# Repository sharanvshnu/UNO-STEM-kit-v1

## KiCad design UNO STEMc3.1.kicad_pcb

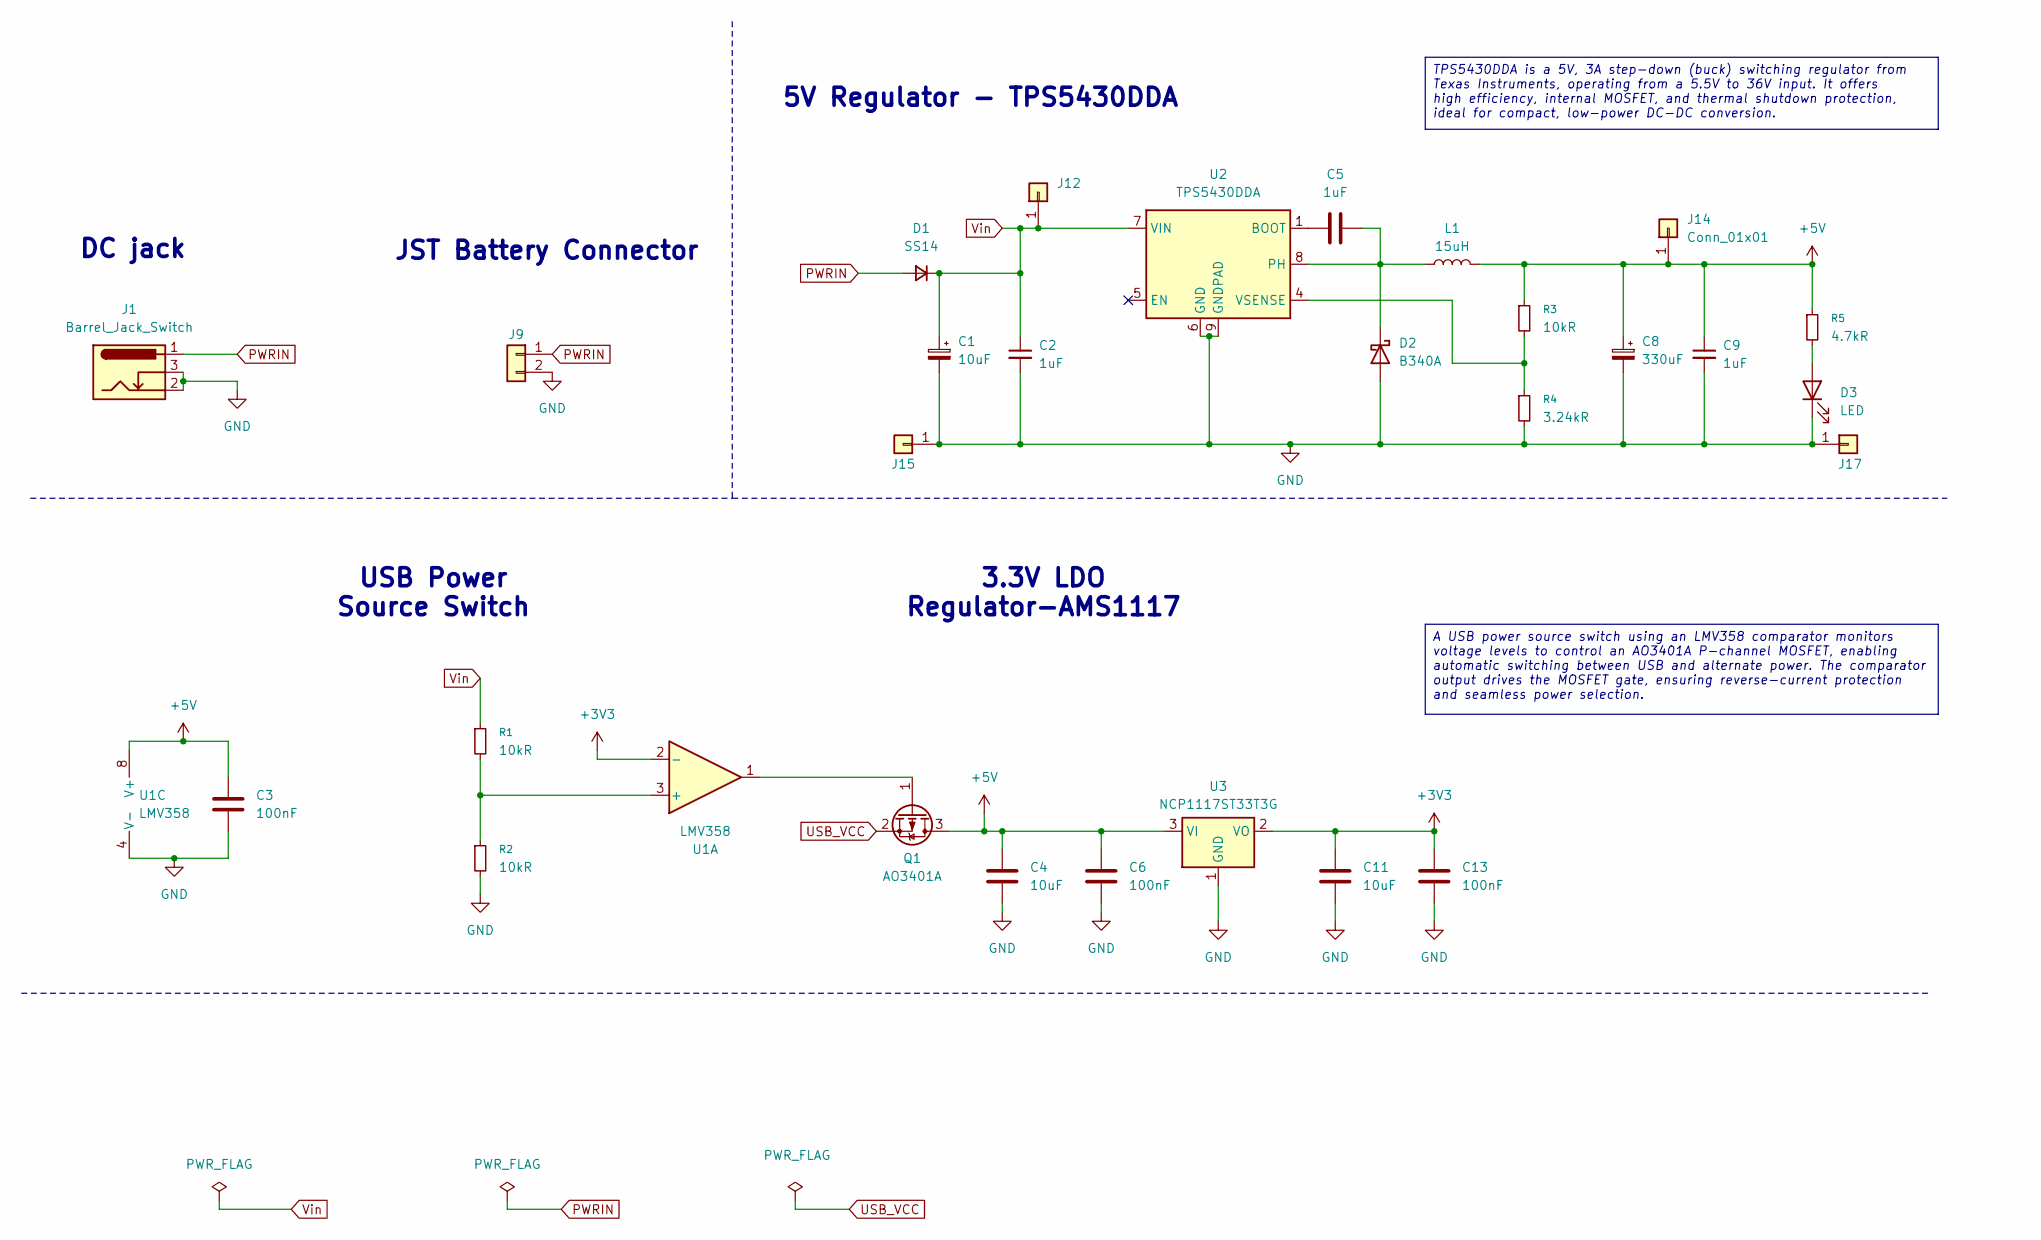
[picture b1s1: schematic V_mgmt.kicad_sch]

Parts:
C1: 10uF; CP_Elec_5x5.3
C2, C5, C9: 1uF; C_0805_2012Metric
C3, C6, C13: 100nF; C_0805_2012Metric
C4, C11: 10uF; C_0805_2012Metric
C8: 330uF; CP_Elec_10x10.5
D1: SS14; D_SMA
D2: B340A; D_SMA
D3: LED; LED_0805_2012Metric
J1: Barrel_Jack_Switch; BarrelJack_GCT_DCJ200-10-A_Horizontal
J9: Conn_01x02; PinHeader_1x02_P2.54mm_Vertical
J12, J14, J15, J17: Conn_01x01; PinHeader_1x01_P2.54mm_Vertical
L1: 15uH; L_10.4x10.4_H4.8
Q1: AO3401A; SOT-23
R1, R2, R3: 10kR; R_0402_1005Metric
R4: 3.24kR; R_0402_1005Metric
R5: 4.7kR; R_0402_1005Metric
U1: LMV358; SOIC-8_3.9x4.9mm_P1.27mm
U2: TPS5430DDA; TI_SO-PowerPAD-8_ThermalVias
U3: NCP1117ST33T3G; SOT-223-3_TabPin2

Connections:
+3V3: C11.1, C13.1, U1.2 (-), U3.2 (VO); also elsewhere on the board
+5V: C3.1, C4.1, C6.1, C8.1, C9.1, J14.1, L1.2, Q1.3 (D), R3.1, R5.1, U1.8 (V+), U3.3 (VI); also elsewhere on the board
GND: C1.2, C2.2, C3.2, C4.2, C6.2, C8.2, C9.2, C11.2, C13.2, D2.2 (A), D3.1 (K), J1.2, J1.3, J9.2, J15.1, J17.1, R2.2, R4.2, U1.4 (V-), U2.6 (GND), U2.9 (GNDPAD), U3.1 (GND); also elsewhere on the board
unnamed: C5.2, D2.1 (K), L1.1, U2.8 (PH)
unnamed: D3.2 (A), R5.2
unnamed: Q1.1 (G), U1.1
unnamed: R1.2, R2.1, U1.3 (+)
unnamed: C5.1, U2.1 (BOOT)
unnamed: R3.2, R4.1, U2.4 (VSENSE)
PWRIN: D1.2 (A), J1.1, J9.1
USB_VCC: Q1.2 (S); also elsewhere on the board
Vin: C1.1, C2.1, D1.1 (K), J12.1, R1.1, U2.7 (VIN)

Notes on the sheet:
JST Battery Connector
3.3V LDO Regulator-AMS1117
5V Regulator - TPS5430DDA
USB Power Source Switch
DC jack
TPS5430DDA is a 5V, 3A step-down (buck) switching regulator from Texas Instruments, operating from a 5.5V to 36V input. It offers high efficiency, internal MOSFET, and thermal shutdown protection, ideal for compact, low-power DC-DC conversion.
A USB power source switch using an LMV358 comparator monitors voltage levels to control an AO3401A P-channel MOSFET, enabling automatic switching between USB and alternate power. The comparator output drives the MOSFET gate, ensuring reverse-current protection and seamless power selection.

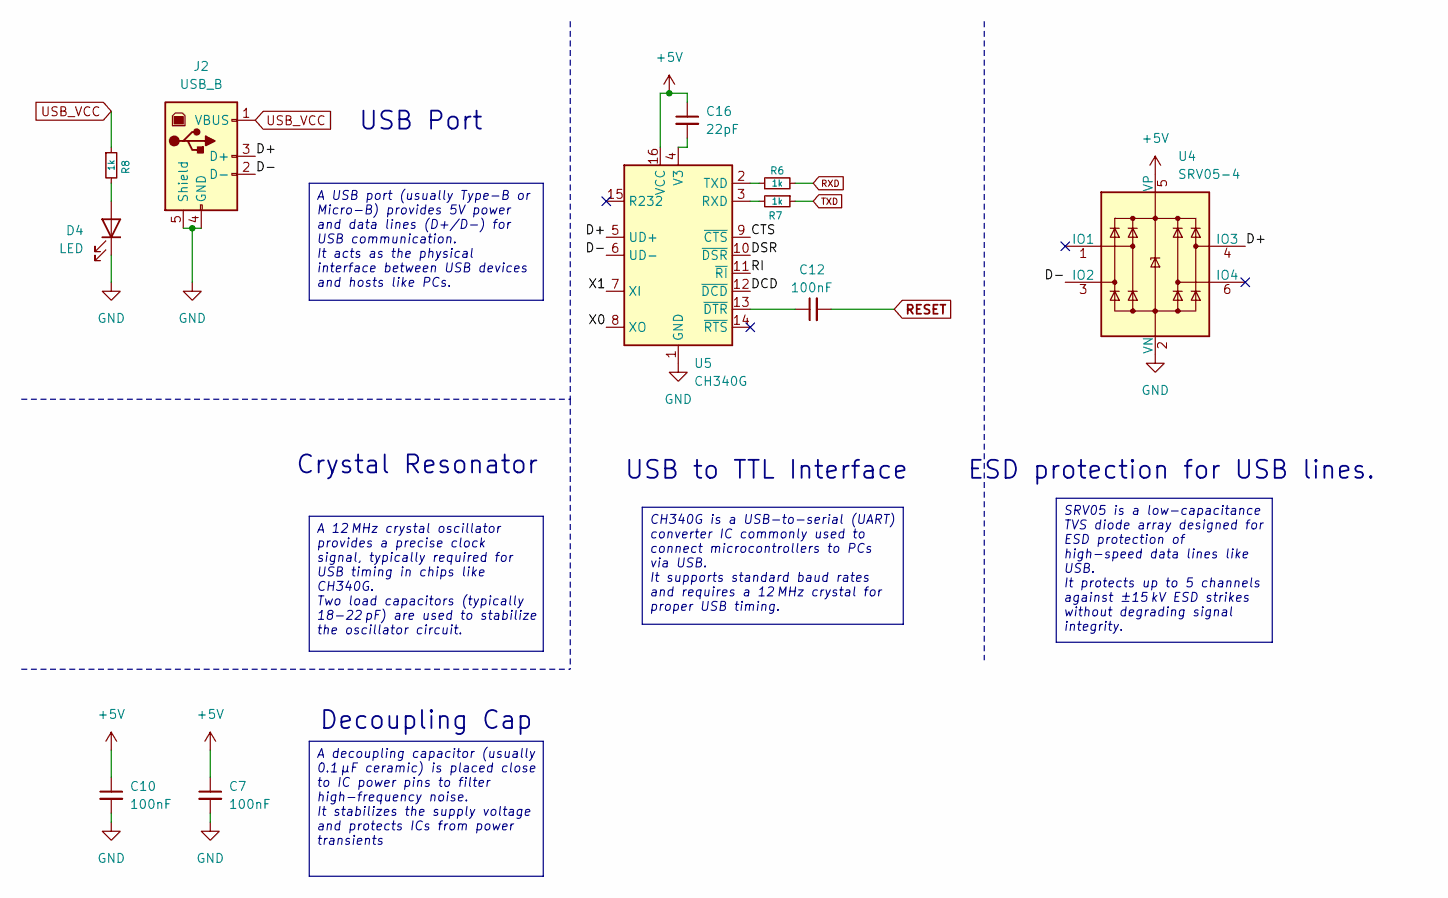
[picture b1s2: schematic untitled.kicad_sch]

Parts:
C7, C10, C12: 100nF; C_0805_2012Metric
C16: 22pF; C_0805_2012Metric
D4: LED; LED_0805_2012Metric
J2: USB_B; USB_B_Lumberg_2411_02_Horizontal
R6, R7: 1k; R_0402_1005Metric
R8: 1k; R_0603_1608Metric
U4: SRV05-4; SOT-23-6
U5: CH340G; SOIC-16_3.9x9.9mm_P1.27mm

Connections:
+5V: C7.1, C10.1, C16.1, U4.5 (VP), U5.16 (VCC); also elsewhere on the board
/USB-TTL/CTS: U5.9 (~CTS)
/USB-TTL/D+: J2.3 (D+), U4.4 (IO3), U5.5 (UD+)
/USB-TTL/D-: J2.2 (D-), U4.3 (IO2), U5.6 (UD-)
/USB-TTL/DCD: U5.12 (~DCD)
/USB-TTL/DSR: U5.10 (~DSR)
/USB-TTL/RI: U5.11 (~RI)
/USB-TTL/X0: U5.8 (XO)
/USB-TTL/X1: U5.7 (XI)
GND: C7.2, C10.2, D4.1 (K), J2.4 (GND), J2.5 (Shield), U4.2 (VN), U5.1 (GND); also elsewhere on the board
unnamed: D4.2 (A), R8.2
unnamed: R7.2, U5.3 (RXD)
unnamed: R6.1, U5.2 (TXD)
unnamed: C16.2, U5.4 (V3)
unnamed: C12.1, U5.13 (~DTR)
RESET: C12.2; also elsewhere on the board
RXD: R6.2; also elsewhere on the board
TXD: R7.1; also elsewhere on the board
USB_VCC: J2.1 (VBUS), R8.1; also elsewhere on the board

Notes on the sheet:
Crystal Resonator
USB to TTL Interface
Decoupling Cap
ESD protection for USB lines.
USB Port
SRV05 is a low-capacitance TVS diode array designed for ESD protection of high-speed data lines like USB. It protects up to 5 channels against ±15 kV ESD strikes without degrading signal integrity.
A USB port (usually Type-B or Micro-B) provides 5V power and data lines (D+/D−) for USB communication. It acts as the physical interface between USB devices and hosts like PCs.
A decoupling capacitor (usually 0.1 µF ceramic) is placed close to IC power pins to filter high-frequency noise. It stabilizes the supply voltage and protects ICs from power transients
A 12 MHz crystal oscillator provides a precise clock signal, typically required for USB timing in chips like CH340G. Two load capacitors (typically 18-22 pF) are used to stabilize the oscillator circuit.
CH340G is a USB-to-serial (UART) converter IC commonly used to connect microcontrollers to PCs via USB. It supports standard baud rates and requires a 12 MHz crystal for proper USB timing.

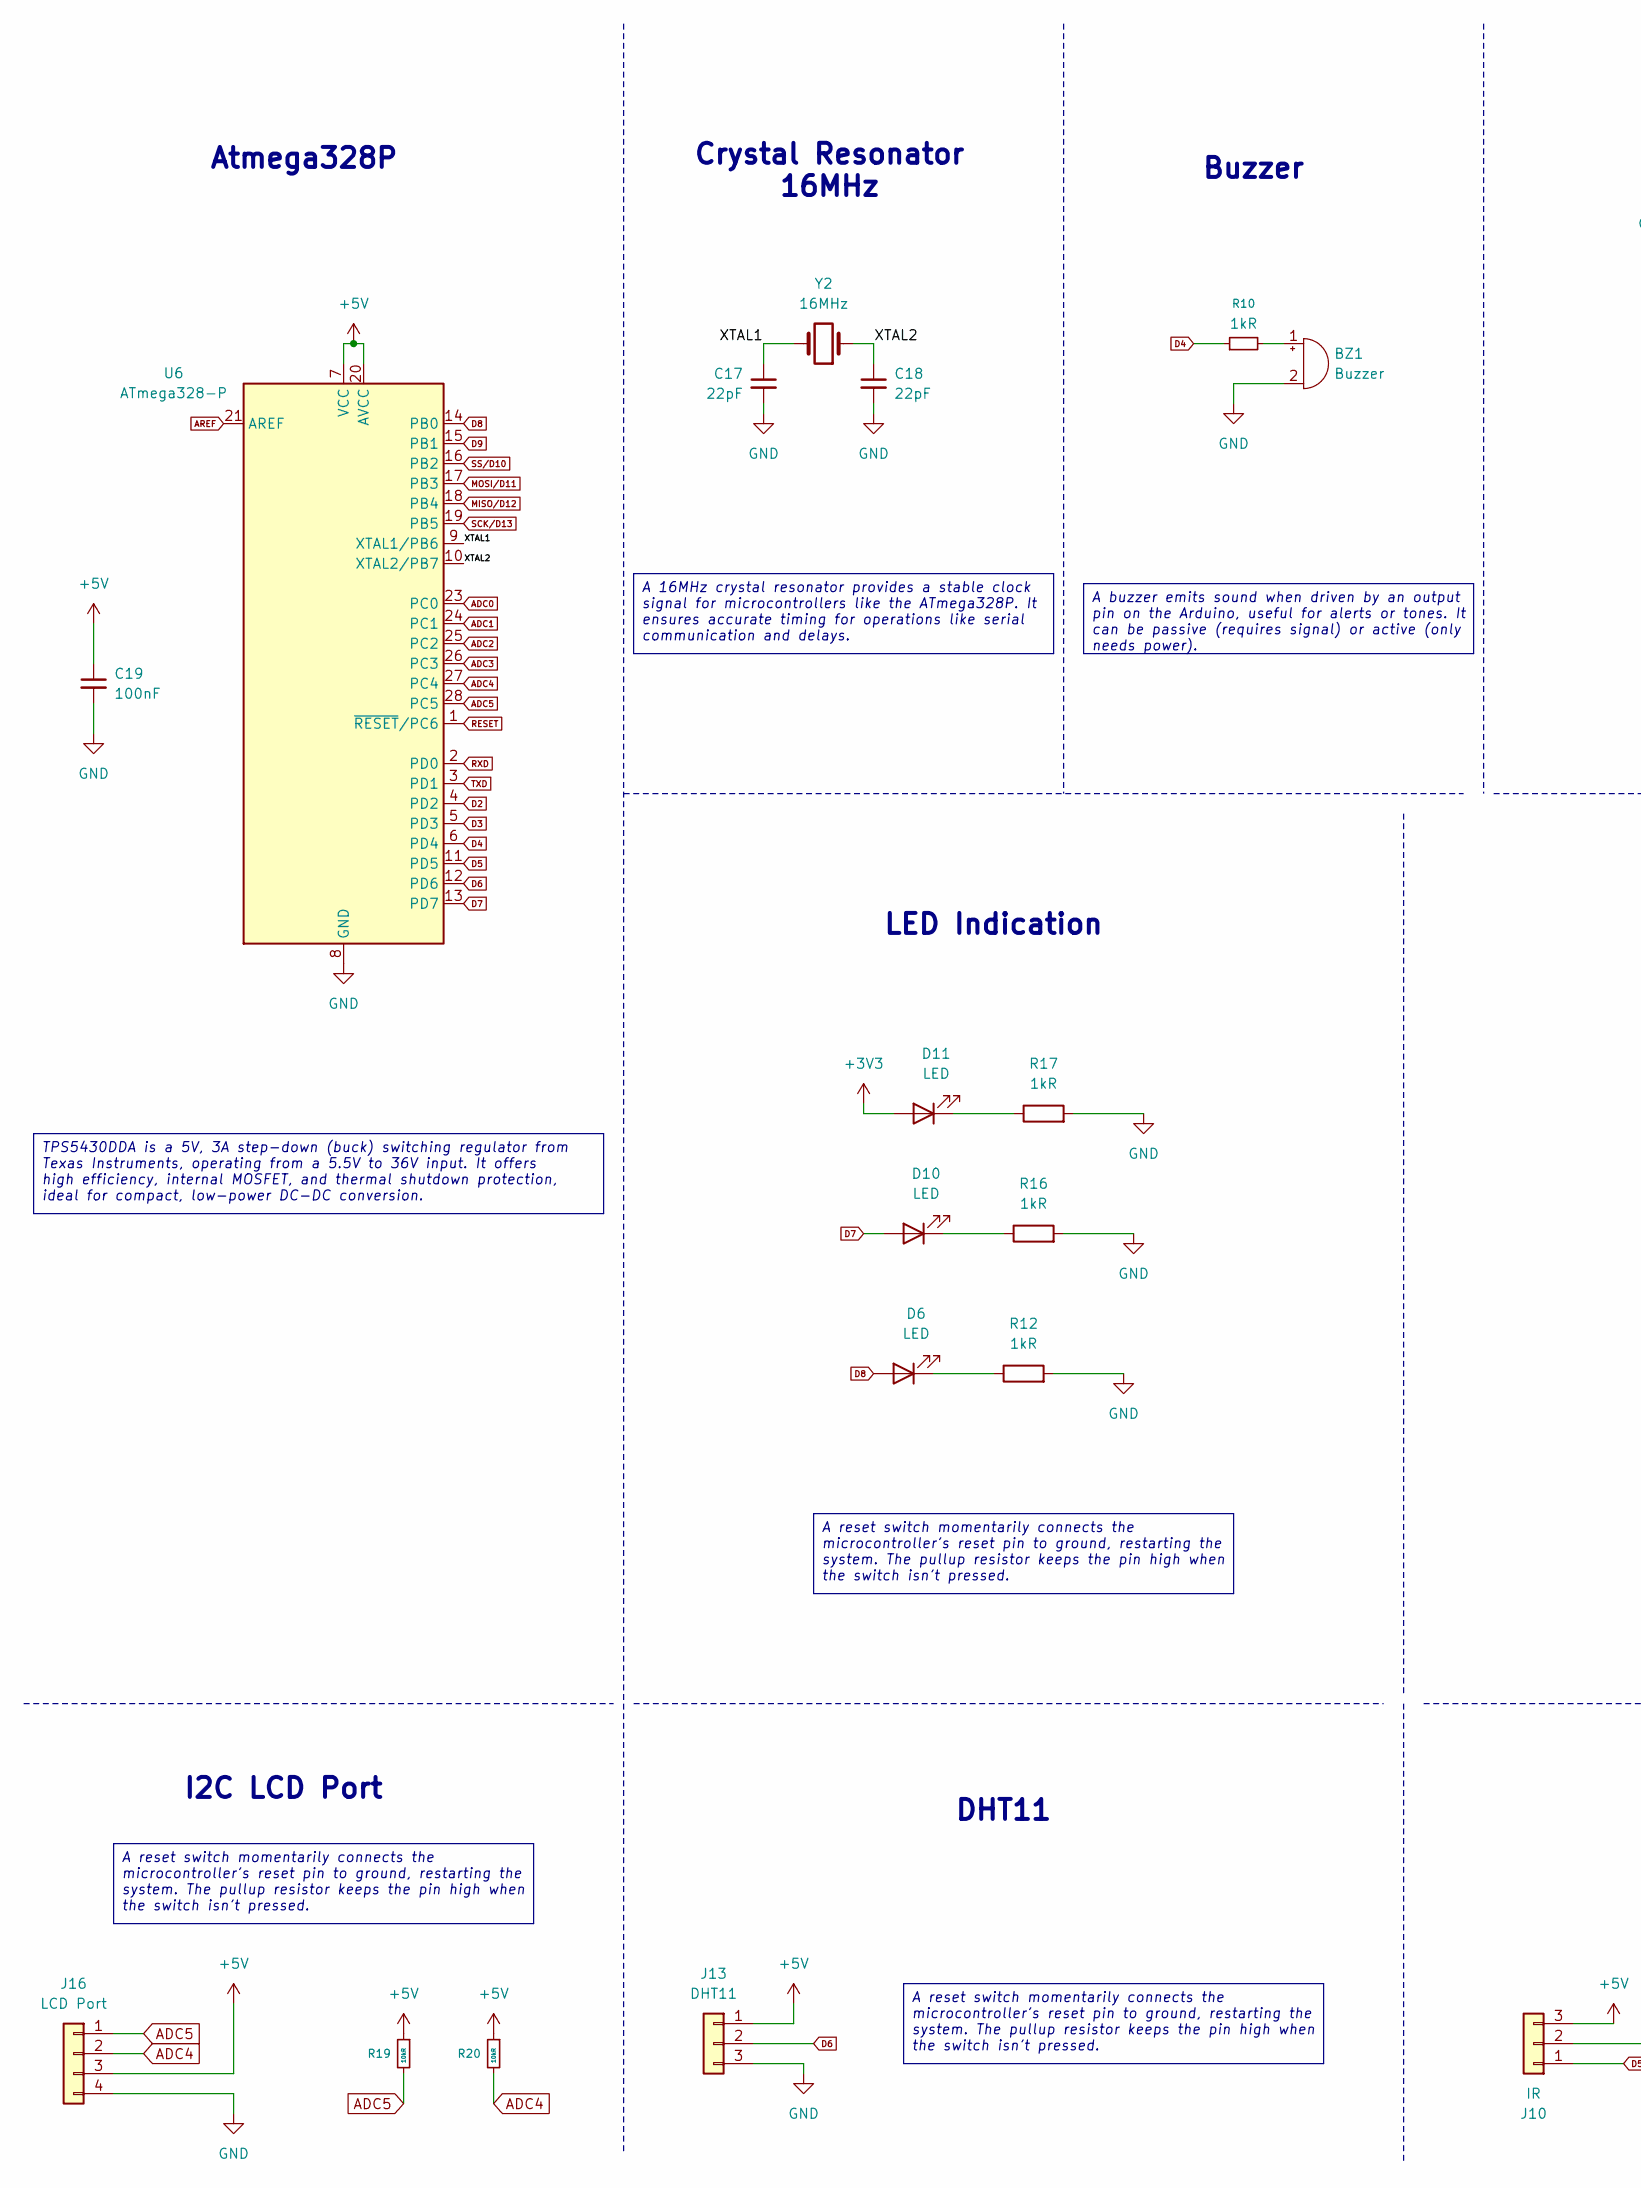
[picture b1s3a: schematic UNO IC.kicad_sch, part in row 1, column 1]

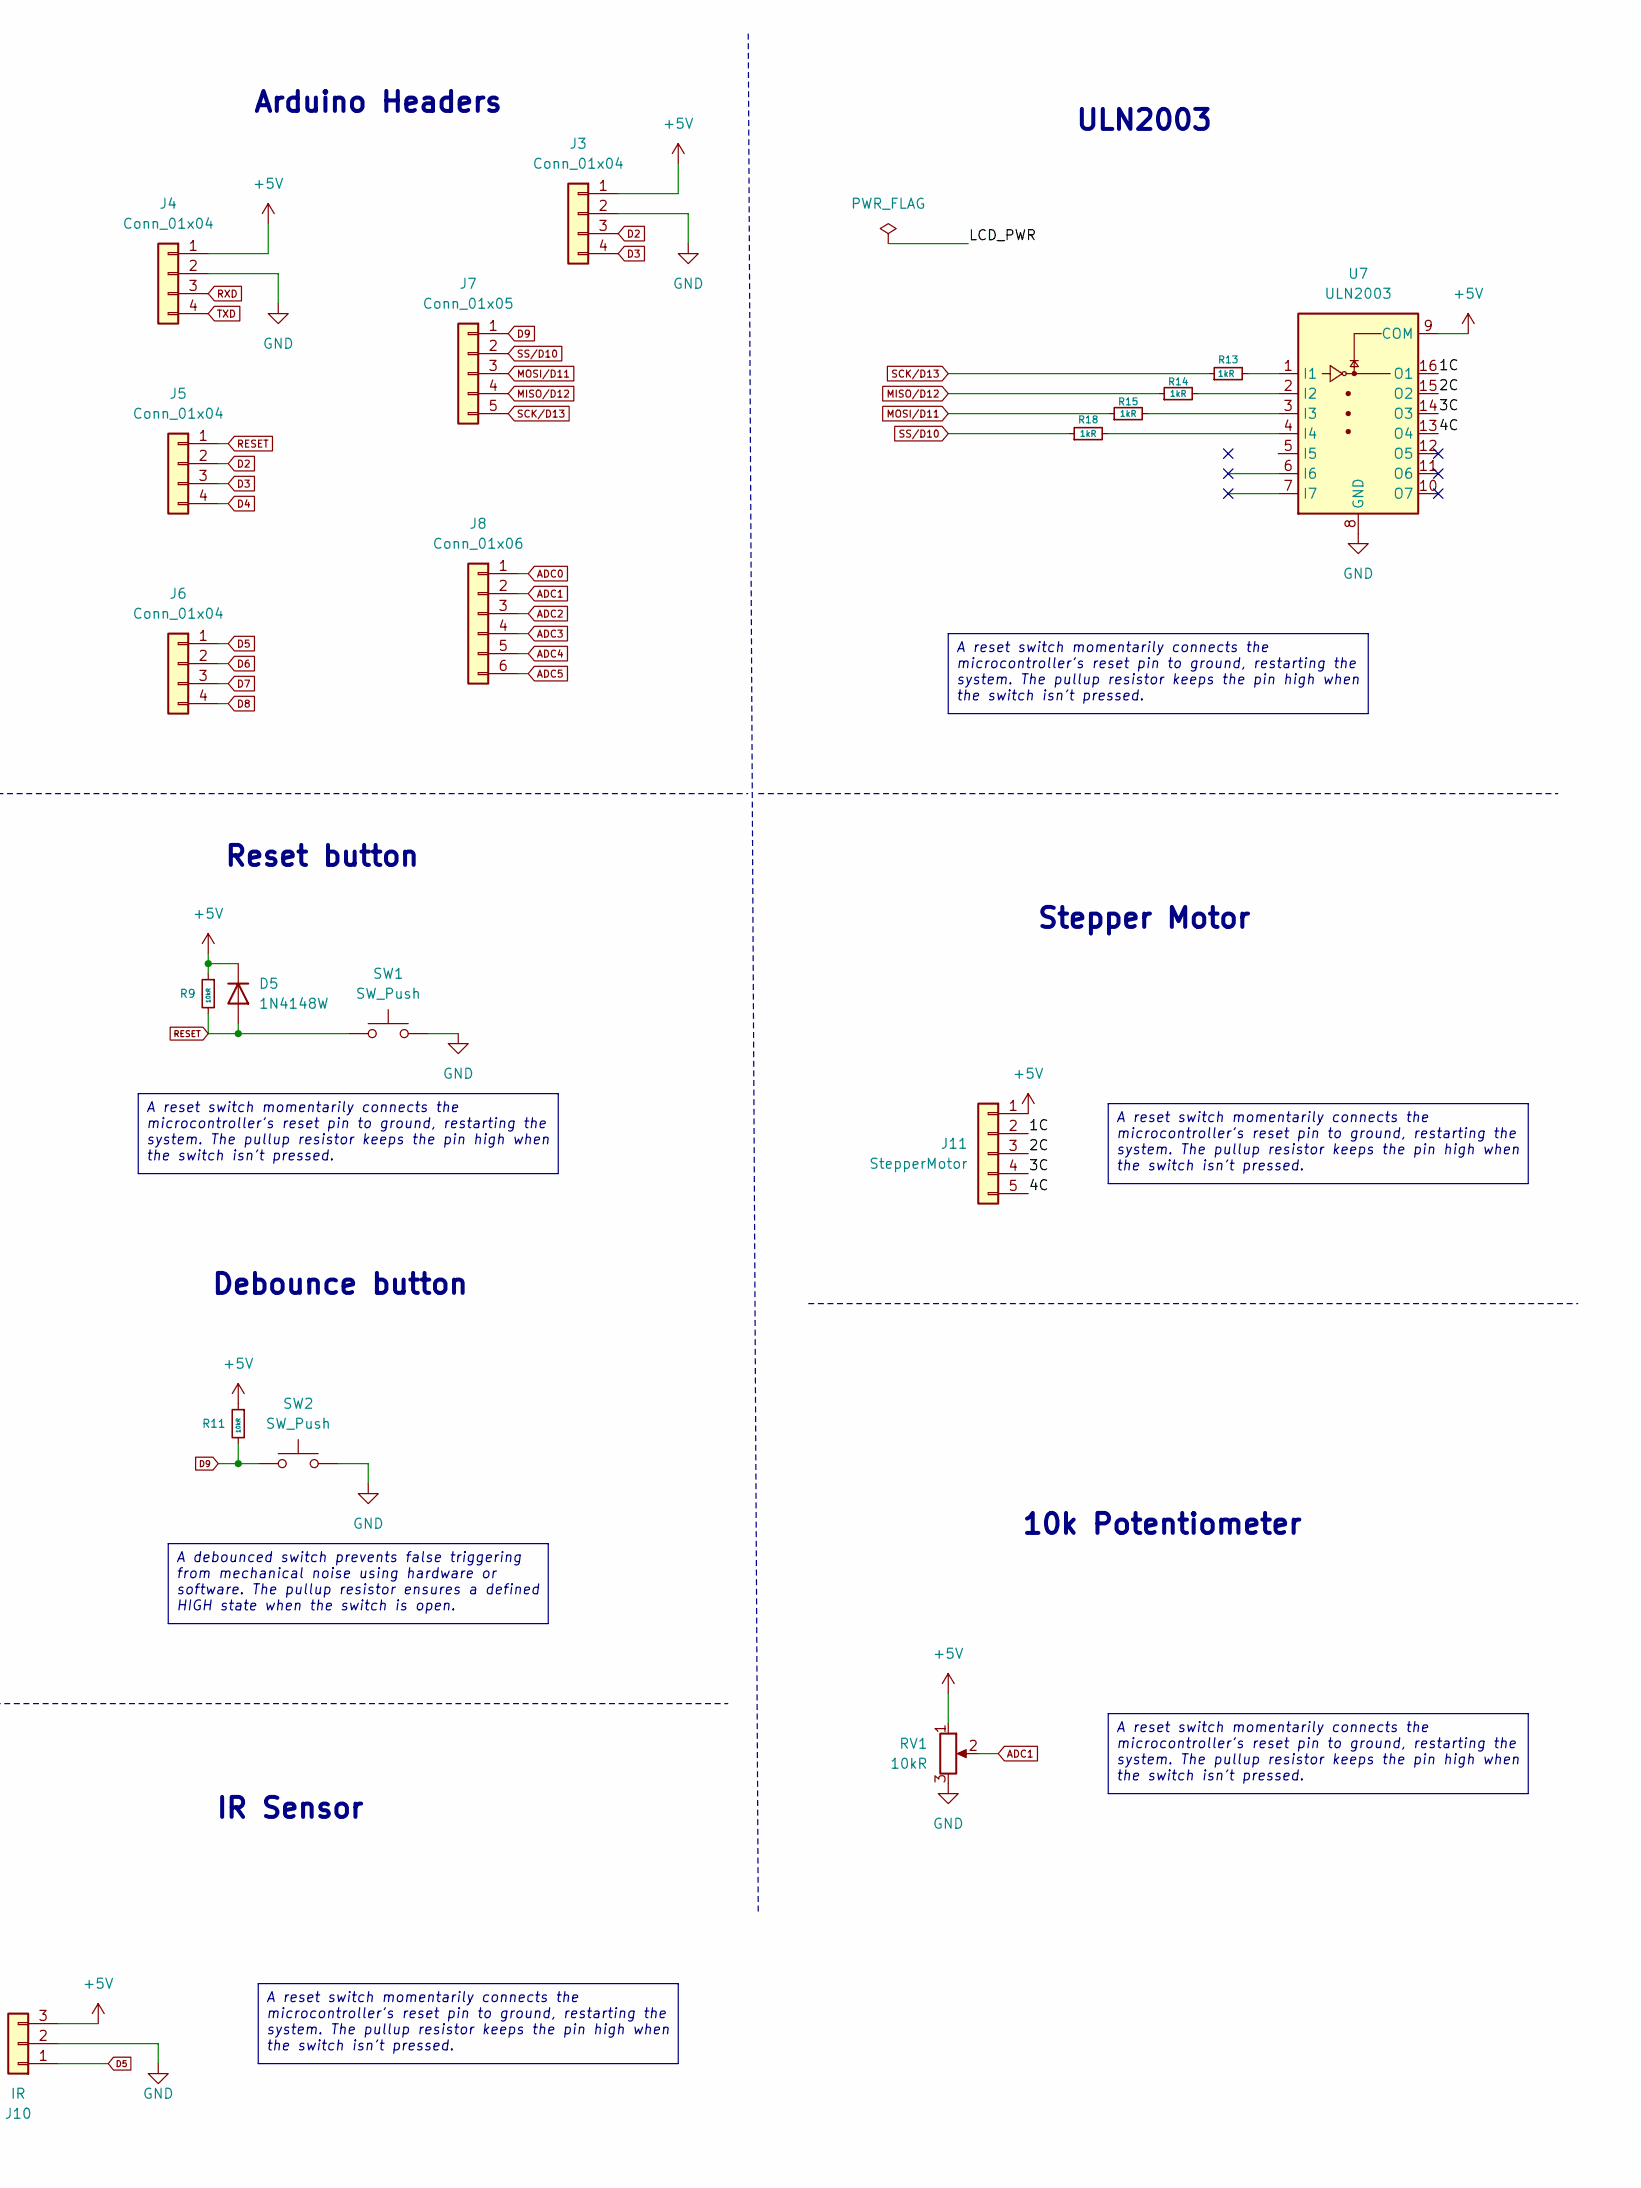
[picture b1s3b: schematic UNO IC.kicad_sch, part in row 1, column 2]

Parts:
BZ1: Buzzer; Buzzer_12x9.5RM7.6
C17, C18: 22pF; C_0805_2012Metric
C19: 100nF; C_0805_2012Metric
D5: 1N4148W; D_SOD-123
D6, D10, D11: LED; LED_0805_2012Metric
J3, J4: Conn_01x04; JST_EH_B4B-EH-A_1x04_P2.50mm_Vertical
J5, J6: Conn_01x04; PinHeader_1x04_P2.54mm_Vertical
J7: Conn_01x05; PinHeader_1x05_P2.54mm_Vertical
J8: Conn_01x06; PinHeader_1x06_P2.54mm_Vertical
J10: IR; JST_EH_B3B-EH-A_1x03_P2.50mm_Vertical
J11: StepperMotor; JST_EH_B5B-EH-A_1x05_P2.50mm_Vertical
J13: DHT11; JST_EH_B3B-EH-A_1x03_P2.50mm_Vertical
J16: LCD Port; JST_EH_B4B-EH-A_1x04_P2.50mm_Vertical
R9, R11, R19, R20: 10kR; R_0402_1005Metric
R10, R12, R13, R14, R15, R16, R17, R18: 1kR; R_0402_1005Metric
RV1: 10kR; Potentiometer_Runtron_RM-065_Vertical
SW1, SW2: SW_Push; SW_PUSH_6mm_H4.3mm
U6: ATmega328-P; DIP-28_W7.62mm
U7: ULN2003; SOIC-16W_5.3x10.2mm_P1.27mm
Y2: 16MHz; Crystal_HC49-4H_Vertical

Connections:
+3V3: D11.2 (A); also elsewhere on the board
+5V: C19.1, D5.1 (K), J3.1, J4.1, J10.3, J11.1, J13.1, J16.3, R9.1, R11.1, R19.1, R20.1, RV1.1, U6.7 (VCC), U6.20 (AVCC), U7.9 (COM); also elsewhere on the board
/Atmega328-PU/1C: J11.2, U7.16 (O1)
/Atmega328-PU/2C: J11.3, U7.15 (O2)
/Atmega328-PU/3C: J11.4, U7.14 (O3)
/Atmega328-PU/4C: J11.5, U7.13 (O4)
/Atmega328-PU/XTAL1: C17.1, U6.9 (XTAL1/PB6), Y2.2
/Atmega328-PU/XTAL2: C18.1, U6.10 (XTAL2/PB7), Y2.1
ADC0: J8.1, U6.23 (PC0)
ADC1: J8.2, RV1.2, U6.24 (PC1)
ADC2: J8.3, U6.25 (PC2)
ADC3: J8.4, U6.26 (PC3)
ADC4: J8.5, J16.2, R20.2, U6.27 (PC4)
ADC5: J8.6, J16.1, R19.2, U6.28 (PC5)
AREF: U6.21 (AREF)
D2: J3.3, J5.2, U6.4 (PD2)
D3: J3.4, J5.3, U6.5 (PD3)
D4: J5.4, R10.1, U6.6 (PD4)
D5: J6.1, J10.1, U6.11 (PD5)
D6: J6.2, J13.2, U6.12 (PD6)
D7: D10.2 (A), J6.3, U6.13 (PD7)
D8: D6.2 (A), J6.4, U6.14 (PB0)
D9: J7.1, R11.2, SW2.1, U6.15 (PB1)
GND: BZ1.2 (-), C17.2, C18.2, C19.2, J3.2, J4.2, J10.2, J13.3, J16.4, R12.2, R16.2, R17.2, RV1.3, SW1.2, SW2.2, U6.8 (GND), U6.22 (GND), U7.8 (GND); also elsewhere on the board
MISO/D12: J7.4, R14.1, U6.18 (PB4)
MOSI/D11: J7.3, R15.1, U6.17 (PB3)
unnamed: BZ1.1 (+), R10.2
unnamed: D6.1 (K), R12.1
unnamed: D10.1 (K), R16.1
unnamed: D11.1 (K), R17.1
unnamed: R13.2, U7.1 (I1)
unnamed: R14.2, U7.2 (I2)
unnamed: R15.2, U7.3 (I3)
unnamed: R18.2, U7.4 (I4)
RESET: D5.2 (A), J5.1, R9.2, SW1.1, U6.1 (~RESET/PC6); also elsewhere on the board
RXD: J4.3, U6.2 (PD0); also elsewhere on the board
SCK/D13: J7.5, R13.1, U6.19 (PB5)
SS/D10: J7.2, R18.1, U6.16 (PB2)
TXD: J4.4, U6.3 (PD1); also elsewhere on the board

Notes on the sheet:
Debounce button
DHT11
Buzzer
Reset button
Atmega328P
Arduino Headers
Stepper Motor
ULN2003
LED Indication
I2C LCD Port
Crystal Resonator 16MHz
10k Potentiometer
IR Sensor
A 16MHz crystal resonator provides a stable clock signal for microcontrollers like the ATmega328P. It ensures accurate timing for operations like serial communication and delays.
TPS5430DDA is a 5V, 3A step-down (buck) switching regulator from Texas Instruments, operating from a 5.5V to 36V input. It offers high efficiency, internal MOSFET, and thermal shutdown protection, ideal for compact, low-power DC-DC conversion.
A reset switch momentarily connects the microcontroller's reset pin to ground, restarting the system. The pullup resistor keeps the pin high when the switch isn't pressed.
A debounced switch prevents false triggering from mechanical noise using hardware or software. The pullup resistor ensures a defined HIGH state when the switch is open.
A buzzer emits sound when driven by an output pin on the Arduino, useful for alerts or tones. It can be passive (requires signal) or active (only needs power).

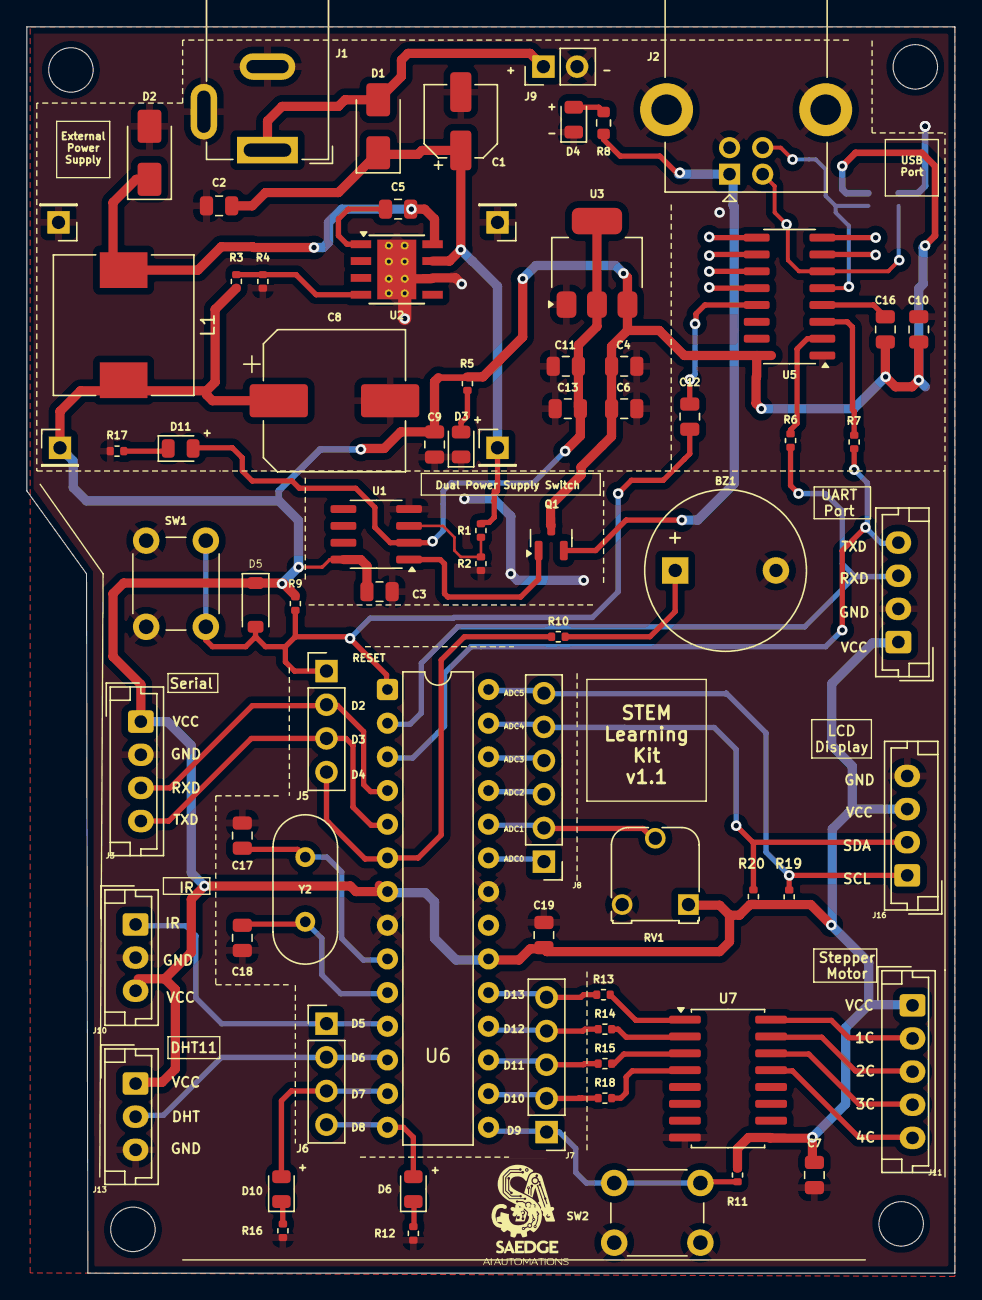
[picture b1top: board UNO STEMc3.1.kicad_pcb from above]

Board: 2 copper layers, 70.0 x 94.0 mm, 76 parts (1 on the bottom side), 54 nets.

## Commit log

2025-12-02 Add files via upload
    The final version of UNO-STEM-v1
